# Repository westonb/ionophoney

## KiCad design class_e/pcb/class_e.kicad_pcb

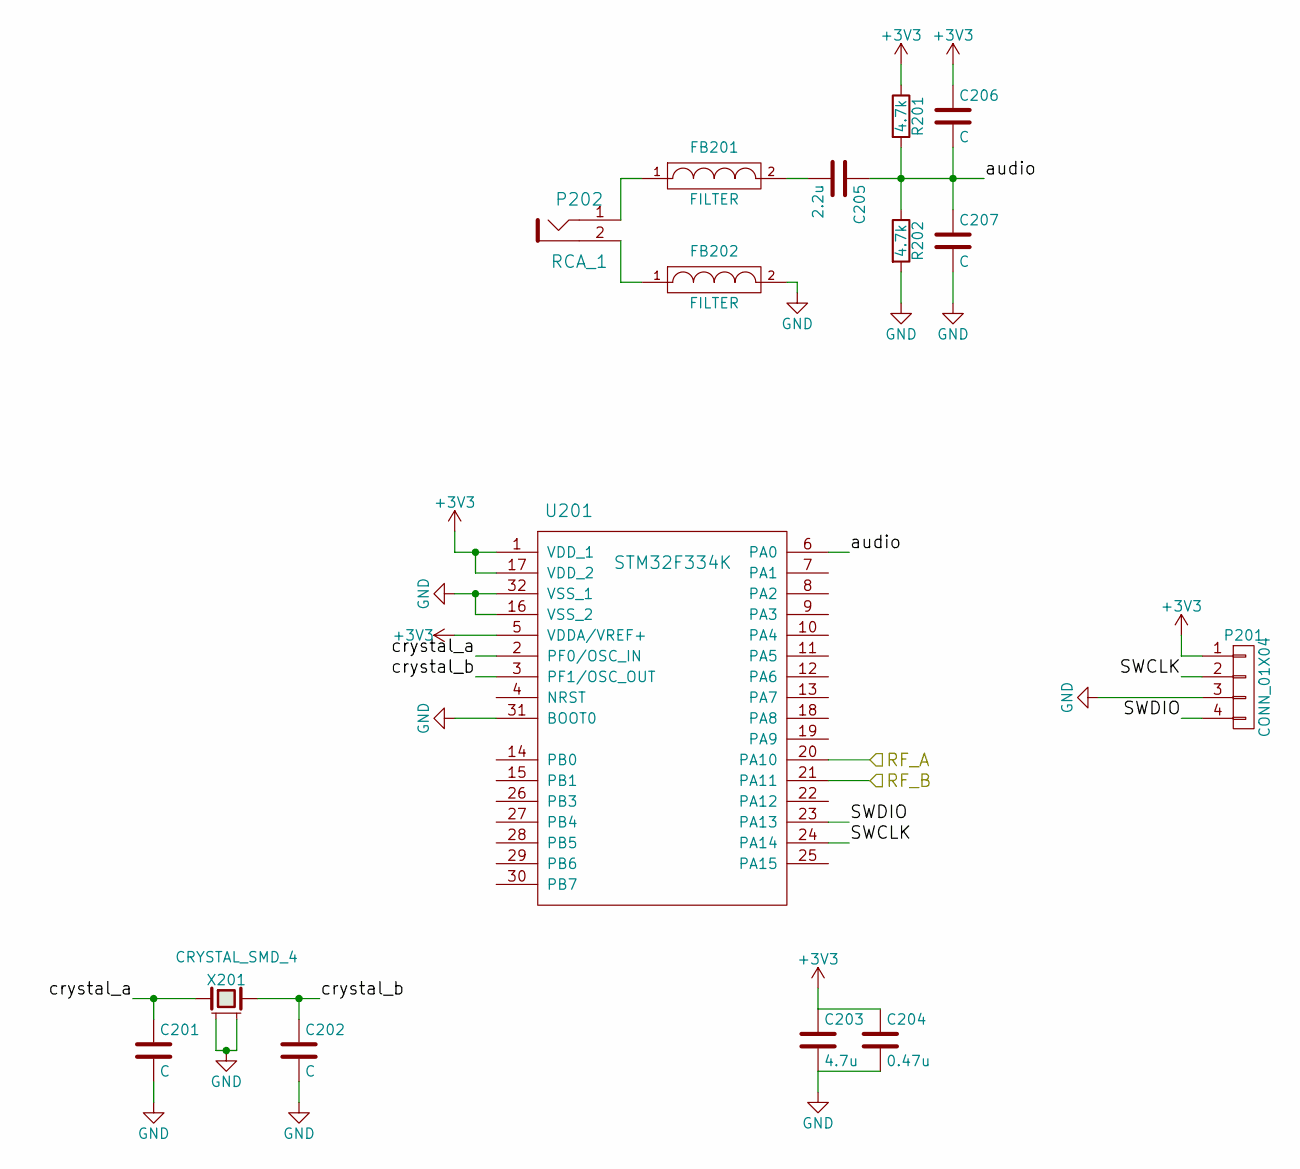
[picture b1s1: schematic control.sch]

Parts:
C201, C202, C206, C207: C; C_0603
C203: 4.7u; C_0603
C204: 0.47u; C_0603
C205: 2.2u; C_0603
FB201, FB202: FILTER; C_0805
P201: CONN_01X04; Pin_Header_Straight_1x04
P202: RCA_1; RCA
R201, R202: 4.7k; R_0603
U201: STM32F334K; LQFP-32_7x7mm_Pitch0.8mm
X201: CRYSTAL_SMD_4; Crystal_3.2x2.5

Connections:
+3V3: C203.1, C204.1, C206.1, P201.1, R201.1, U201.1 (VDD_1), U201.5 (VDDA/VREF+), U201.17 (VDD_2); also elsewhere on the board
/Control/RF_A: U201.20 (PA10); also elsewhere on the board
/Control/RF_B: U201.21 (PA11); also elsewhere on the board
/Control/SWCLK: P201.2, U201.24 (PA14)
/Control/SWDIO: P201.4, U201.23 (PA13)
/Control/audio: C205.1, C206.2, C207.1, R201.2, R202.1, U201.6 (PA0)
/Control/crystal_a: C201.1, U201.2 (PF0/OSC_IN), X201.1
/Control/crystal_b: C202.1, U201.3 (PF1/OSC_OUT), X201.3
GND: C201.2, C202.2, C203.2, C204.2, C207.2, FB202.2, P201.3, R202.2, U201.16 (VSS_2), U201.31 (BOOT0), U201.32 (VSS_1), X201.2, X201.4; also elsewhere on the board
unnamed: C205.2, FB201.2
unnamed: FB201.1, P202.1
unnamed: FB202.1, P202.2

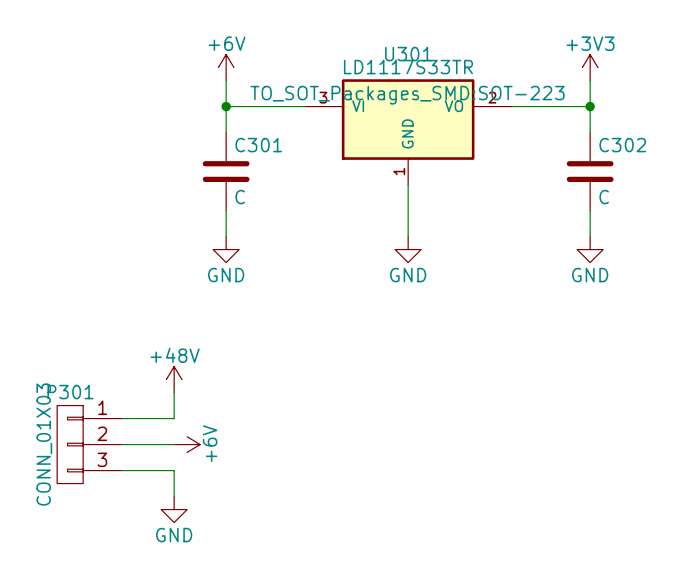
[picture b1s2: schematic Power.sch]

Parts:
C301, C302: C; C_0603
P301: CONN_01X03; terminalBlock-3.5mm-3
U301: LD1117S33TR; SOT-223

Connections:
+3V3: C302.1, U301.2 (VO); also elsewhere on the board
+6V: C301.1, P301.2, U301.3 (VI); also elsewhere on the board
+48V: P301.1; also elsewhere on the board
GND: C301.2, C302.2, P301.3, U301.1 (GND); also elsewhere on the board

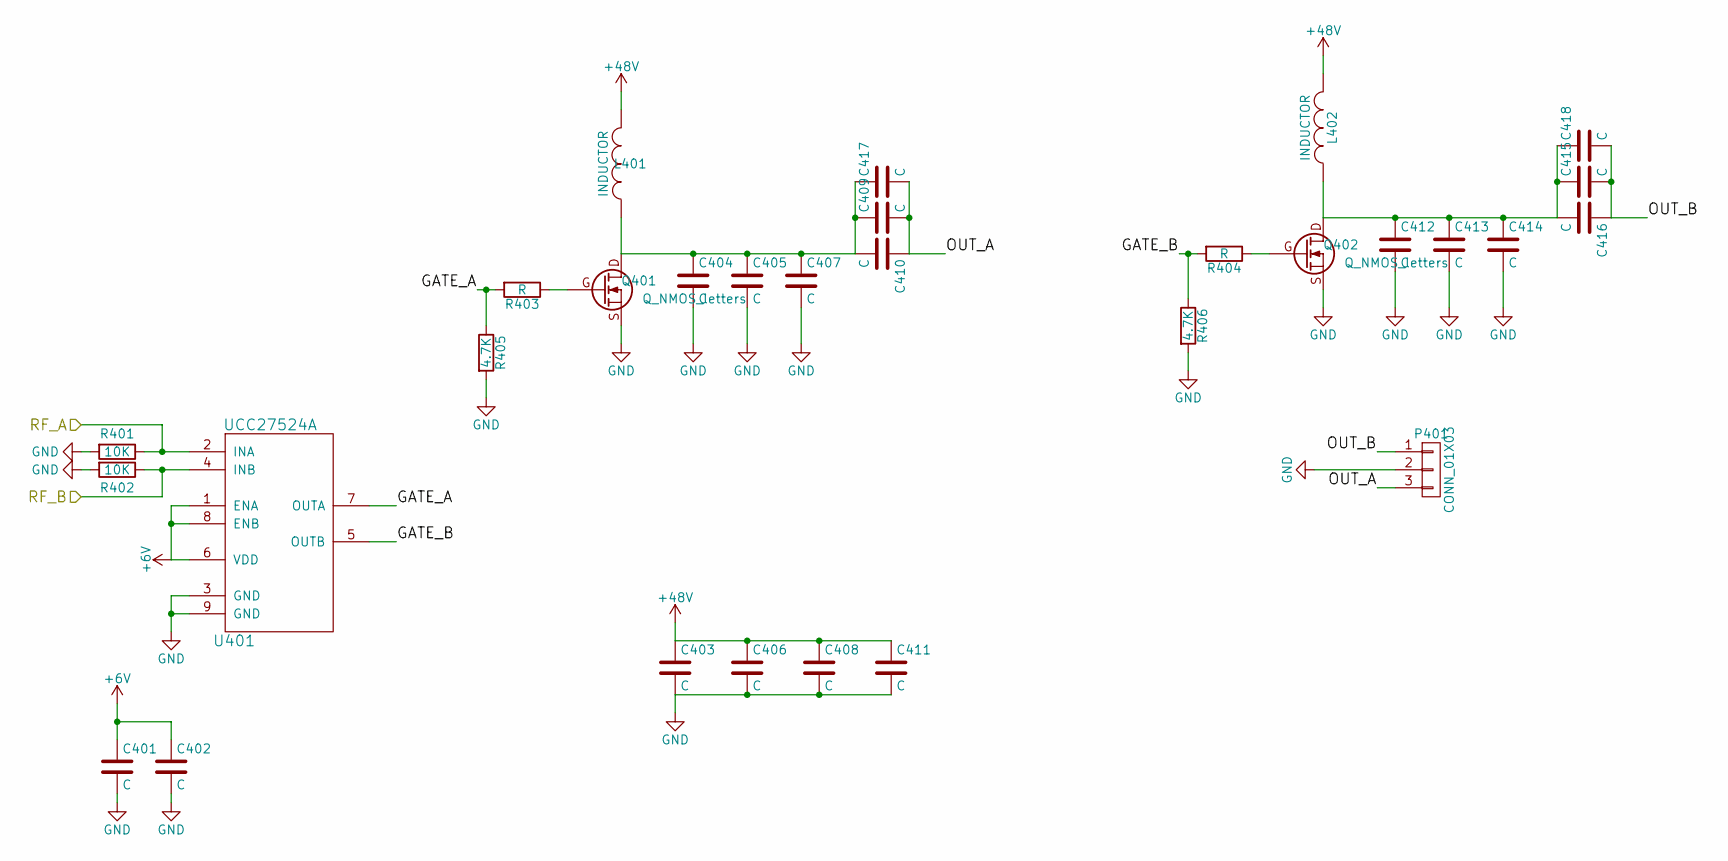
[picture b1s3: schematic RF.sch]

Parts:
C401, C402: C; C_0603
C403, C404, C405, C406, C407, C408, C409, C410, C411, C412, C413, C414, C415, C416, C417, C418: C; C_1206
L401, L402: INDUCTOR; 2929SQ
P401: CONN_01X03; terminalBlock-3.5mm-3
Q401, Q402: Q_NMOS_letters; GS66508T
R401, R402: 10K; R_0603
R403, R404: R; R_0805
R405, R406: 4.7K; R_0603
U401: UCC27524A; SOIC-8-1EP_3.9x4.9mm_Pitch1.27mm

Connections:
+6V: C401.1, C402.1, U401.1 (ENA), U401.6 (VDD), U401.8 (ENB); also elsewhere on the board
+48V: C403.1, C406.1, C408.1, C411.1, L401.2, L402.2; also elsewhere on the board
/Control/RF_A: R401.1, U401.2 (INA); also elsewhere on the board
/Control/RF_B: R402.1, U401.4 (INB); also elsewhere on the board
/RF/GATE_A: R403.2, R405.1, U401.7 (OUTA)
/RF/GATE_B: R404.2, R406.1, U401.5 (OUTB)
/RF/OUT_A: C409.2, C410.1, C417.2, P401.3
/RF/OUT_B: C415.2, C416.1, C418.2, P401.1
GND: C401.2, C402.2, C403.2, C404.2, C405.2, C406.2, C407.2, C408.2, C411.2, C412.2, C413.2, C414.2, P401.2, Q401.S, Q402.S, R401.2, R402.2, R405.2, R406.2, U401.3 (GND), U401.9 (GND); also elsewhere on the board
unnamed: C404.1, C405.1, C407.1, C409.1, C410.2, C417.1, L401.1, Q401.D
unnamed: C412.1, C413.1, C414.1, C415.1, C416.2, C418.1, L402.1, Q402.D
unnamed: Q401.G, R403.1
unnamed: Q402.G, R404.1

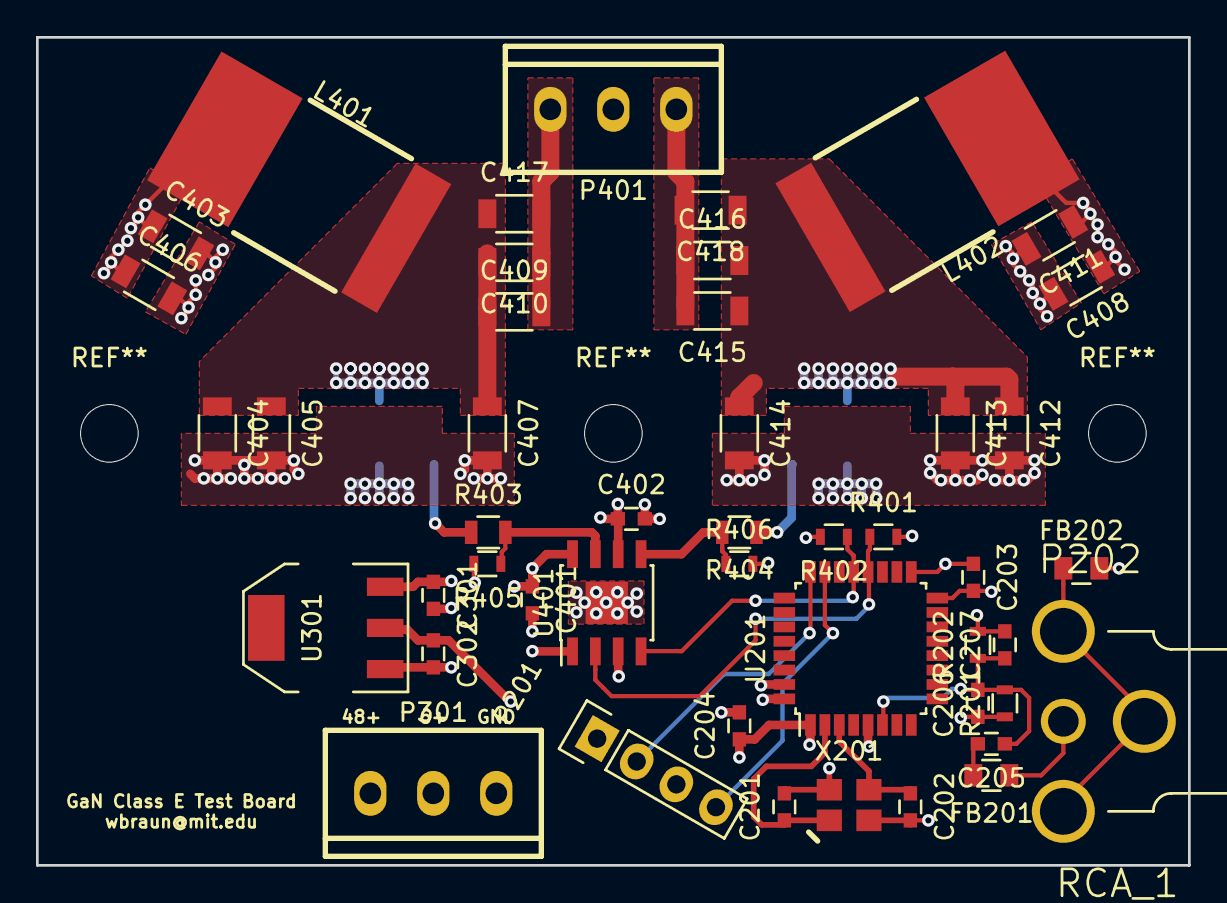
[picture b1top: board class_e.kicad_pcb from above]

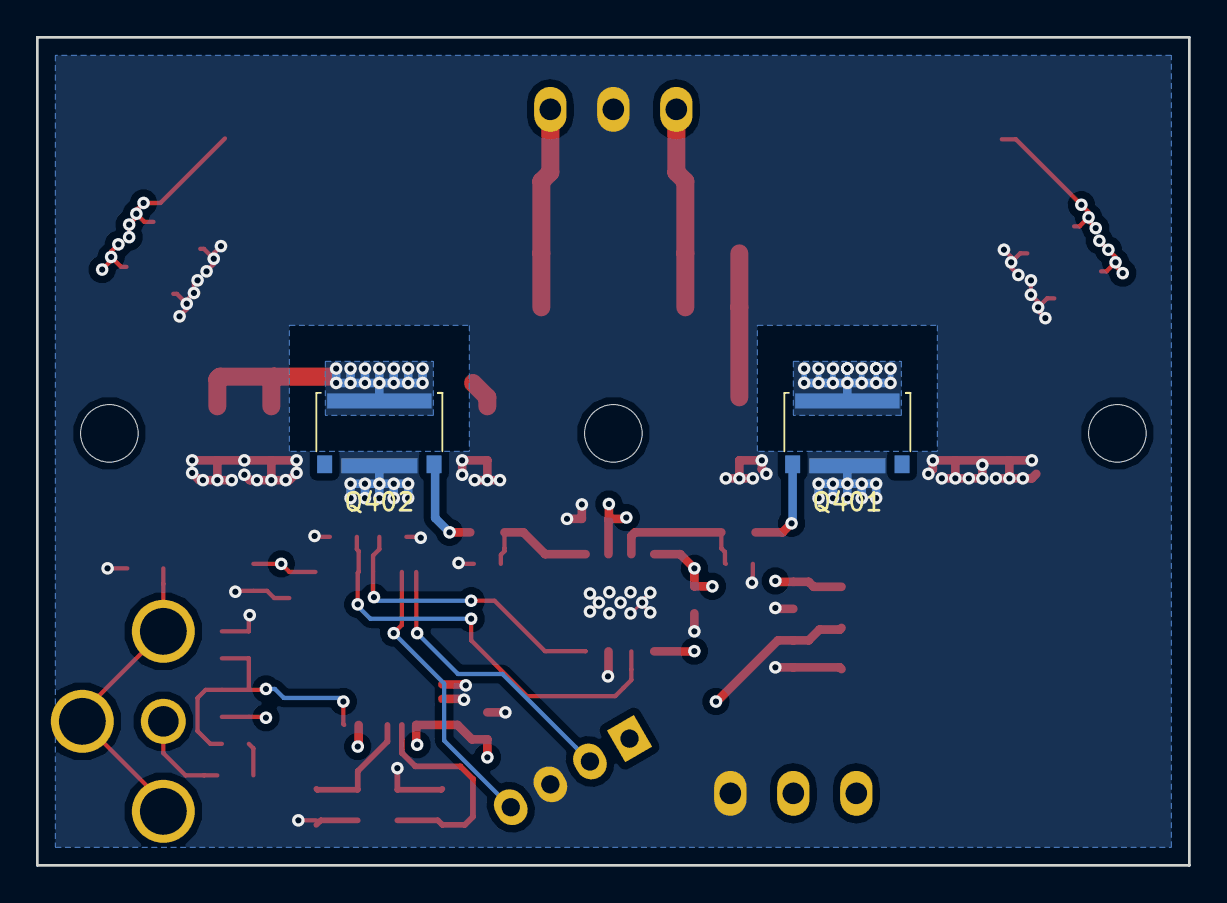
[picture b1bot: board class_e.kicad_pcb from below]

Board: 4 copper layers, 64.0 x 46.0 mm, 49 parts (2 on the bottom side), 22 nets.

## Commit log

2016-04-06 First commit! Schematic topology entered
2016-04-08 added measurements and simulation
2016-11-27 new GaN test board
2016-11-27 slight pcb changes, sent off to fab
2017-01-11 firmware
2017-01-11 trying out outphasing
2017-01-12 pwm works
2017-01-12 audio modulation first test
2017-01-25 differential class E
